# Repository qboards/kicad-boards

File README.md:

# QBoard Printed Circuit Boards

All development boards made in Kicad

## Breakout boards

* [BB-Led](bb-led) - Single SMD (0805) LED breakout board
* [BB-LedBar](bb-ledbar) - Eight SMD (0805) LED breakout board
* [BB-ButtonBar](bb-buttonbar) - Four tactile switch breakout board
* [BB-SOIC-SSOP-8](bb-soic-ssop-8) - Breakout board for SOIC/SSOP ICs up to 8 pins
* [BB-SOIC-SSOP-16](bb-soic-ssop-16) - Breakout board for SOIC/SSOP ICs up to 16 pins
* [BB-SOIC-SSOP-24](bb-soic-ssop-24) - Breakout board for SOIC/SSOP ICs up to 24 pins
* [BB-SOT89-SOT223](bb-sot89-sot223) - Breakout board for SOT-89 / SOT-223 smd transitor packages
* [BB-TQFP-QFN](bb-tqfp-qfn-32) - Breakout board for TQFP/QFN ICs with 32 pins
* [BB-XTAL](bb-xtal) - Breakout board for Crystal and its capacitors
* [BB-AVRISP](bb-avrisp) - Breakout for 10- and 6-pin AVR ISP connectors

## Development tools

* [DEV-UUSBPSU](dev-uusb-psu) - Small 3.3V/5V breadboard power supply with microUSB connector

# About QBoards

QBoard is a project to create a collection of small tools that facilitate Electronic 
Engineering, using readily available parts. For PCBs we aim to create well designed 
boards that can be purchased by low cost vendors such as <a href="https://www.seeedstudio.com">
Seeed Studio</a>, <a href="https://oshpark.com/">OSHPark</a> or <a href="https://dirtypcbs.com">DirtyPCBs</a>.

# Licensing

This work is licensed under a [Creative Commons Attribution-ShareAlike 4.0 International License](http://creativecommons.org/licenses/by-sa/4.0/).

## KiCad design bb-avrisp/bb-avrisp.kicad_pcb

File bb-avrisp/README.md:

# QBoard BB-AVRISP

Breakout for 10 and 6 pin AVR ISP (In-system Programming) connectors

# Downloads

* [Gerbers](output/gerbers.zip)
* [Schematic](output/schematic.pdf)

# Buy

* [Buy protopack (10) from DirtyPcbs](https://dirtypcbs.com/store/designer/details/qboards/6508/qboard-bb-avrisp)

# About QBoards

See [here](https://github.com/qboards/kicad-boards#about-qboards)

# Licensing

See [here](https://github.com/qboards/kicad-boards#licensing)

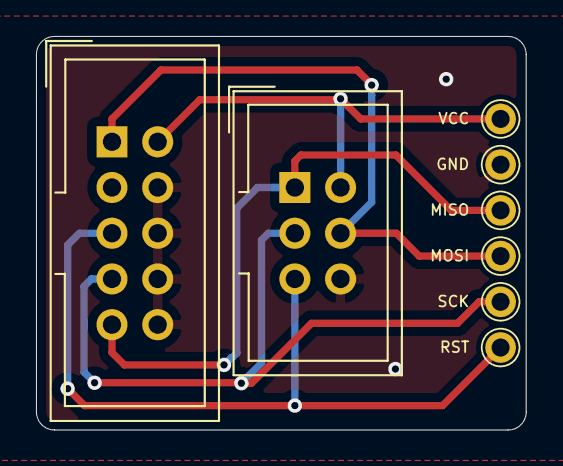
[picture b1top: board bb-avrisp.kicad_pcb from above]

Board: 2 copper layers, 27.2 x 21.9 mm, 9 parts (1 on the bottom side), 6 nets.

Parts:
BB_AVRISP: LOGO_BRD_REF; logo_url-3mm
J1, J2, J3, J4, J5, J8: Conn_01x01_Male; PinHeader_1x01_P2.54mm_Vertical
J6: Conn_02x03_Odd_Even; IDC-Header_2x03_P2.54mm_Vertical
J7: Conn_02x05_Odd_Even; IDC-Header_2x05_P2.54mm_Vertical

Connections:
GND: J6.6, J7.4, J7.6, J7.8, J7.10, J8.1
MISO: J2.1, J6.1, J7.9
MOSI: J3.1, J6.4, J7.1
RST: J5.1, J6.5, J7.5
SCK: J4.1, J6.3, J7.7
VCC: J1.1, J6.2, J7.2

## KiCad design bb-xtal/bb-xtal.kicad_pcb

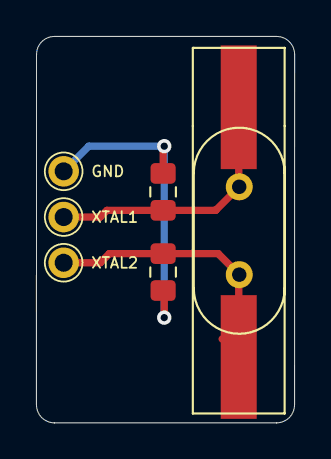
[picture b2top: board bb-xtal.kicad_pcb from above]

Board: 2 copper layers, 14.3 x 21.5 mm, 8 parts (1 on the bottom side), 3 nets.

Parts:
BB_XTAL: LOGO_BRD_REF; logo_url-5mm
C1, C2: C; C_0805_2012Metric_Pad1.15x1.40mm_HandSolder
J1, J2, J3: Conn_01x01_Male; PinHeader_1x01_P2.54mm_Vertical
Y1: Crystal; Crystal_HC49-4H_Vertical
Y2: Crystal; Crystal_SMD_HC49-SD_HandSoldering

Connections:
unnamed: C1.1, J2.1, Y1.1, Y2.1
unnamed: C1.2, C2.1, J3.1
unnamed: C2.2, J1.1, Y1.2, Y2.2

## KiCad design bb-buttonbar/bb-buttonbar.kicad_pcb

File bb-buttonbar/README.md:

# QBoard BB-ButtonBar

Array of 4 tactile switches on a breakout board. Includes (common) pull-up or
pull-down resistor

# Downloads

* [Gerbers](output/gerbers.zip)
* [Schematic](output/schematic.pdf)

# Buy

* [Buy protopack (10) from DirtyPcbs](https://dirtypcbs.com/store/designer/details/qboards/6509/qboard-bb-button-bar)

# About QBoards

See [here](https://github.com/qboards/kicad-boards#about-qboards)

# Licensing

See [here](https://github.com/qboards/kicad-boards#licensing)

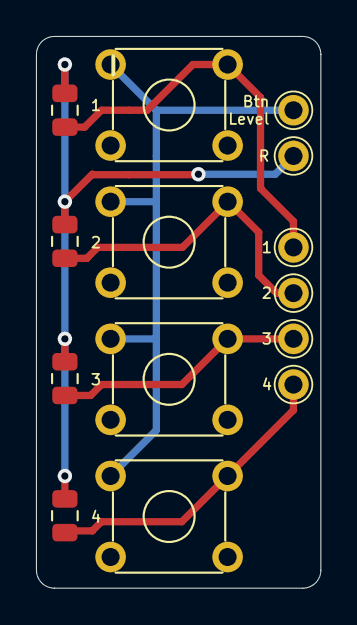
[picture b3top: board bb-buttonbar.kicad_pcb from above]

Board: 2 copper layers, 15.8 x 30.7 mm, 15 parts (1 on the bottom side), 6 nets.

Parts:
1, 2, 3, 4: SW_Push; SW_TH_Tactile_Omron_B3F-10xx
BB_BUTTONBAR: LOGO_BRD_REF; logo_url-3mm
J1, J2, J3, J4: Conn_01x01_Male; PinHeader_1x01_P2.54mm_Vertical_dual
LEVEL1, LEVEL2: Conn_01x01_Male; PinHeader_1x01_P2.54mm_Vertical_dual
R1, R2, R3, R4: R; R_0805_2012Metric

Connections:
unnamed: 1.2, J1.1, R1.2
unnamed: 2.2, J2.1, R2.2
unnamed: 3.2, J3.1, R3.2
unnamed: 4.2, J4.1, R4.2
unnamed: 1.1, 2.1, 3.1, 4.1, LEVEL1.1
unnamed: LEVEL2.1, R1.1, R2.1, R3.1, R4.1

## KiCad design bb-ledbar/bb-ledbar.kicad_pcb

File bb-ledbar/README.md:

# QBoard BB-LedBar

Array of eight SMD leds (0805) on a breakout board that fits between the bus and the main grid of a breadboard. One side is common cathode, other side common anode.

# Downloads

* [Gerbers](output/gerbers.zip)
* [Schematic](output/schematic.pdf)

# Buy

* [Buy protopack (10) from DirtyPcbs](https://dirtypcbs.com/store/designer/details/qboards/6508/qboard-bb-led)

# About QBoards

See [here](https://github.com/qboards/kicad-boards#about-qboards)

# Licensing

See [here](https://github.com/qboards/kicad-boards#licensing)

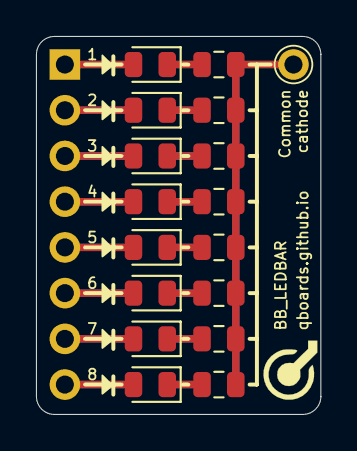
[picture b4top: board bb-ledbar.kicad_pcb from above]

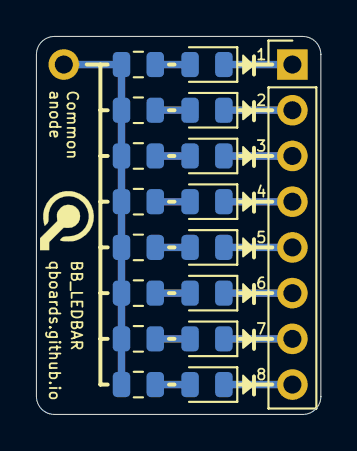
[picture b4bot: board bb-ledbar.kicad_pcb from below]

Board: 2 copper layers, 15.8 x 21.0 mm, 36 parts (18 on the bottom side), 25 nets.

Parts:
BB_LEDBAR: LOGO_BRD_REF; logo_url-3mm
BB_LEDBAR#2: LOGO_BRD_REF; logo_url-3mm
DA_1, DA_2, DA_3, DA_4, DA_5, DA_6, DA_7, DA_8: LED; LED_0805_2012Metric
DB_1, DB_2, DB_3, DB_4, DB_5, DB_6, DB_7, DB_8: LED; LED_0805_2012Metric
J1: Conn_01x08_Male; PinHeader_1x08_P2.54mm_Vertical
J2: Conn_01x01_Male; PinHeader_1x01_P2.54mm_Vertical
RA_1, RA_2, RA_3, RA_4, RA_5, RA_6, RA_7, RA_8: R; R_0805_2012Metric
RB_1, RB_2, RB_3, RB_4, RB_5, RB_6, RB_7, RB_8: R; R_0805_2012Metric

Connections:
unnamed: DA_1.1, RA_1.1
unnamed: DA_1.2, DB_1.1, J1.1
unnamed: DA_2.1, RA_2.1
unnamed: DA_2.2, DB_2.1, J1.2
unnamed: DA_3.1, RA_3.1
unnamed: DA_3.2, DB_3.1, J1.3
unnamed: DA_4.1, RA_4.1
unnamed: DA_4.2, DB_4.1, J1.4
unnamed: DA_5.1, RA_5.1
unnamed: DA_5.2, DB_5.1, J1.5
unnamed: DA_6.1, RA_6.1
unnamed: DA_6.2, DB_6.1, J1.6
unnamed: DA_7.1, RA_7.1
unnamed: DA_7.2, DB_7.1, J1.7
unnamed: DA_8.1, RA_8.1
unnamed: DA_8.2, DB_8.1, J1.8
unnamed: DB_1.2, RB_1.1
unnamed: DB_2.2, RB_2.1
unnamed: DB_3.2, RB_3.1
unnamed: DB_4.2, RB_4.1
unnamed: DB_5.2, RB_5.1
unnamed: DB_6.2, RB_6.1
unnamed: DB_7.2, RB_7.1
unnamed: DB_8.2, RB_8.1
unnamed: J2.1, RA_1.2, RA_2.2, RA_3.2, RA_4.2, RA_5.2, RA_6.2, RA_7.2, RA_8.2, RB_1.2, RB_2.2, RB_3.2, RB_4.2, RB_5.2, RB_6.2, RB_7.2, RB_8.2

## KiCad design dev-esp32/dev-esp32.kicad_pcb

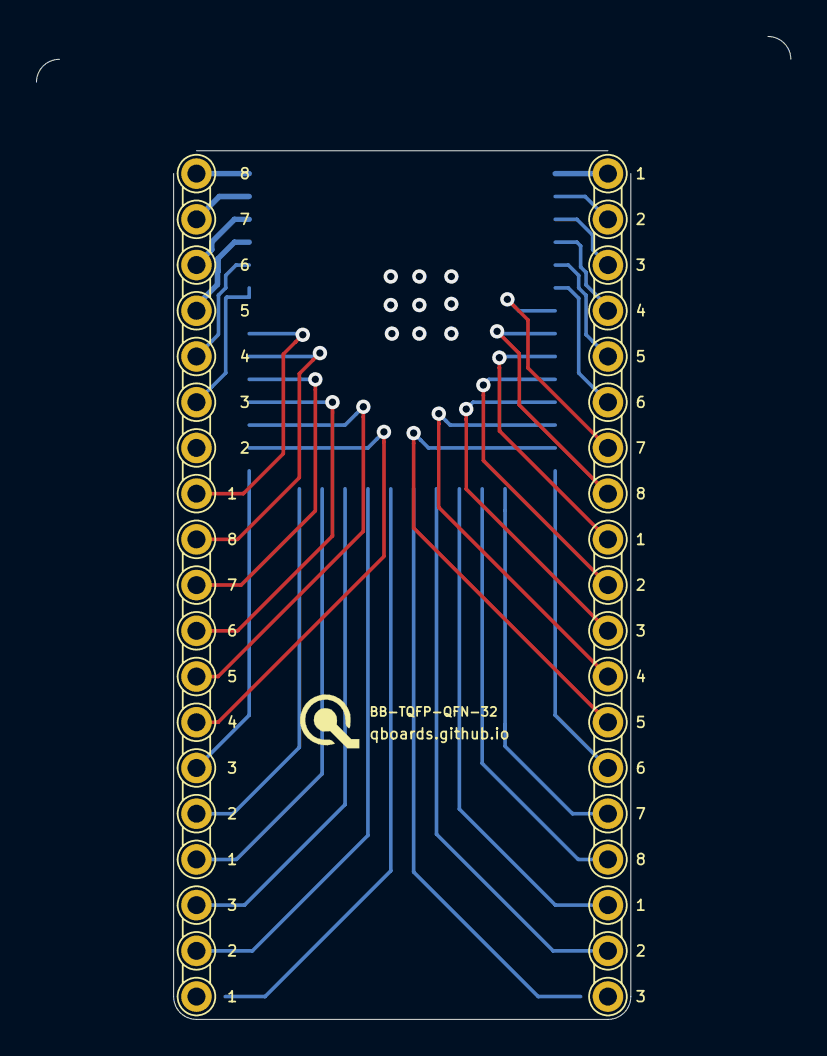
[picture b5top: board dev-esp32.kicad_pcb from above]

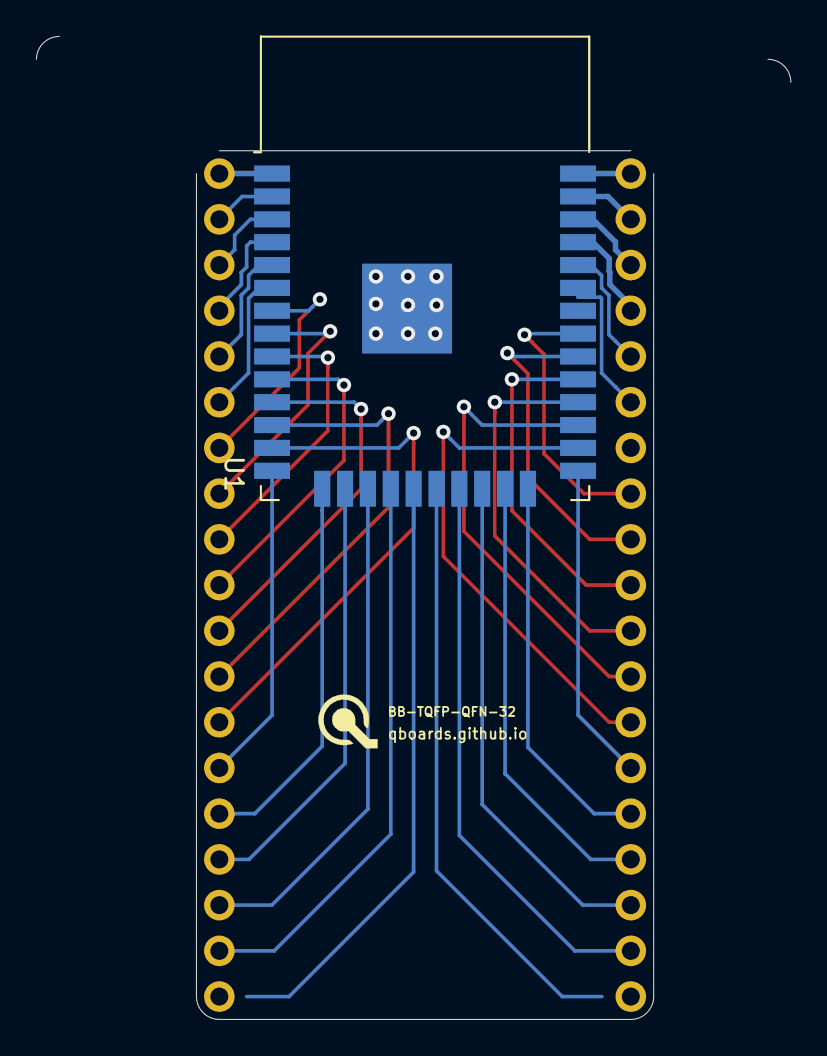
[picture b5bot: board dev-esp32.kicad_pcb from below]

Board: 2 copper layers, 41.9 x 54.6 mm, 9 parts (2 on the bottom side), 35 nets.

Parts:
BB-TQFP-QFN-32, BB-TQFP-QFN-32#2: LOGO_BRD_REF; logo_url-3mm
J1_8, J9_16, J23_30, J31_38: Conn_01x08_Male; PinHeader_1x08_P2.54mm_Vertical
J17_19, J20_22: Conn_01x03_Male; PinHeader_1x03_P2.54mm_Vertical
U1: ESP32-WROOM-32

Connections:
unnamed: J1_8.1, J9_16.7, J31_38.8, U1.1, U1.15, U1.38
unnamed: J1_8.2, U1.2
unnamed: J1_8.3, U1.3
unnamed: J1_8.4, U1.4
unnamed: J1_8.5, U1.5
unnamed: J1_8.6, U1.6
unnamed: J1_8.7, U1.7
unnamed: J1_8.8, U1.8
unnamed: J9_16.1, U1.9
unnamed: J9_16.2, U1.10
unnamed: J9_16.3, U1.11
unnamed: J9_16.4, U1.12
unnamed: J9_16.5, U1.13
unnamed: J9_16.6, U1.14
unnamed: J9_16.8, U1.16
unnamed: J17_19.1, U1.17
unnamed: J17_19.2, U1.18
unnamed: J17_19.3, U1.19
unnamed: J20_22.1, U1.20
unnamed: J20_22.2, U1.21
unnamed: J20_22.3, U1.22
unnamed: J23_30.1, U1.23
unnamed: J23_30.2, U1.24
unnamed: J23_30.3, U1.25
unnamed: J23_30.4, U1.26
unnamed: J23_30.5, U1.27
unnamed: J23_30.6, U1.28
unnamed: J23_30.7, U1.29
unnamed: J23_30.8, U1.30
unnamed: J31_38.1, U1.31
unnamed: J31_38.3, U1.33
unnamed: J31_38.4, U1.34
unnamed: J31_38.5, U1.35
unnamed: J31_38.6, U1.36
unnamed: J31_38.7, U1.37

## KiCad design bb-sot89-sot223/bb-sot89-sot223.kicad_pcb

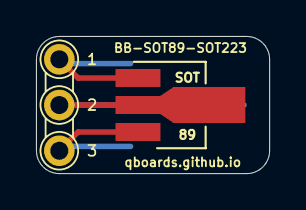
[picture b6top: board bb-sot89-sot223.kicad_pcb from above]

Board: 2 copper layers, 13.0 x 7.6 mm, 3 parts (1 on the bottom side), 3 nets.

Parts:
J1: Conn_01x03_Male; PinHeader_1x03_P2.54mm_Vertical_dual
SOT: AZ1117-3.3; SOT-89-3_Handsoldering
SOT-223: LM337_SOT223; SOT-223-3_TabPin2

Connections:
unnamed: J1.1, SOT.1, SOT-223.3
unnamed: J1.2, SOT.2, SOT-223.2
unnamed: J1.3, SOT.3, SOT-223.1

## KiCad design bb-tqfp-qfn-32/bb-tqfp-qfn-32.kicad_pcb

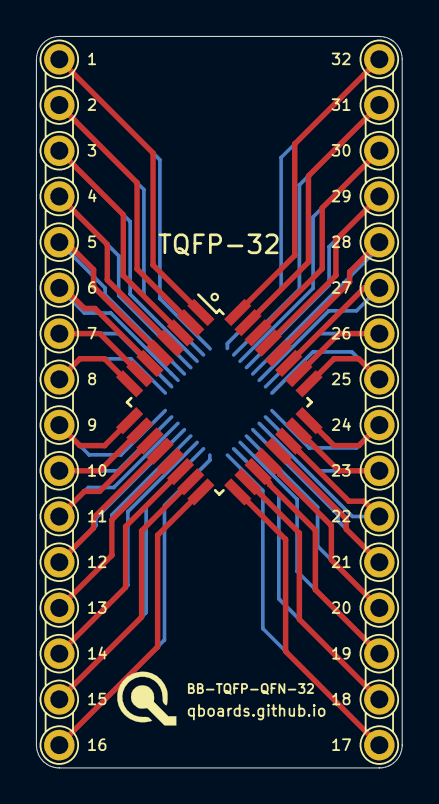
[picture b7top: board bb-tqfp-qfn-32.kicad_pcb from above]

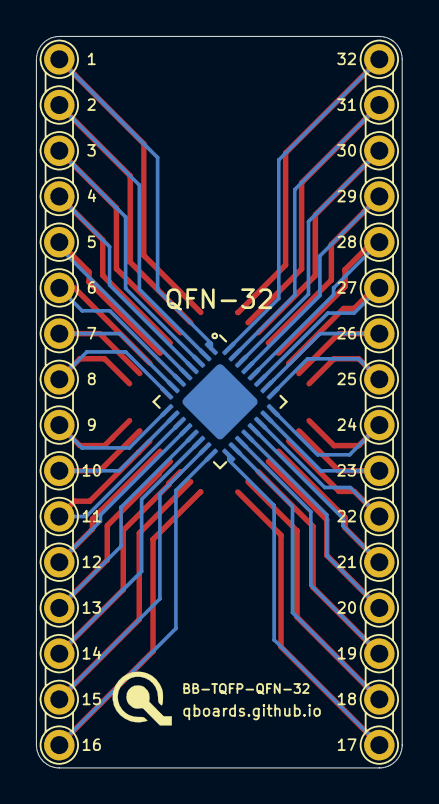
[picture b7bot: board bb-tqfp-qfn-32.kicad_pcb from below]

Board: 2 copper layers, 20.3 x 40.6 mm, 8 parts (2 on the bottom side), 32 nets.

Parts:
BB-TQFP-QFN-32, BB-TQFP-QFN-32#2: LOGO_BRD_REF; logo_url-3mm
J1, J2, J3, J4: Conn_01x08_Male; PinHeader_1x08_P2.54mm_Vertical_dual
QFN-32: IC-32Q; QFN-32-1EP_5x5mm_P0.5mm_EP3.1x3.1mm
TQFP-32: IC-32Q; TQFP-32_7x7mm_P0.8mm

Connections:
unnamed: J1.1, QFN-32.32, TQFP-32.1
unnamed: J1.2, QFN-32.31, TQFP-32.2
unnamed: J1.3, QFN-32.30, TQFP-32.3
unnamed: J1.4, QFN-32.29, TQFP-32.4
unnamed: J1.5, QFN-32.28, TQFP-32.5
unnamed: J1.6, QFN-32.27, TQFP-32.6
unnamed: J1.7, QFN-32.26, TQFP-32.7
unnamed: J1.8, QFN-32.25, TQFP-32.8
unnamed: J2.1, QFN-32.24, TQFP-32.9
unnamed: J2.2, QFN-32.23, TQFP-32.10
unnamed: J2.3, QFN-32.22, TQFP-32.11
unnamed: J2.4, QFN-32.21, TQFP-32.12
unnamed: J2.5, QFN-32.20, TQFP-32.13
unnamed: J2.6, QFN-32.19, TQFP-32.14
unnamed: J2.7, QFN-32.18, TQFP-32.15
unnamed: J2.8, QFN-32.17, TQFP-32.16
unnamed: J3.1, QFN-32.16, TQFP-32.17
unnamed: J3.2, QFN-32.15, TQFP-32.18
unnamed: J3.3, QFN-32.14, TQFP-32.19
unnamed: J3.4, QFN-32.13, TQFP-32.20
unnamed: J3.5, QFN-32.12, TQFP-32.21
unnamed: J3.6, QFN-32.11, TQFP-32.22
unnamed: J3.7, QFN-32.10, TQFP-32.23
unnamed: J3.8, QFN-32.9, TQFP-32.24
unnamed: J4.1, QFN-32.8, TQFP-32.25
unnamed: J4.2, QFN-32.7, TQFP-32.26
unnamed: J4.3, QFN-32.6, TQFP-32.27
unnamed: J4.4, QFN-32.5, TQFP-32.28
unnamed: J4.5, QFN-32.4, TQFP-32.29
unnamed: J4.6, QFN-32.3, TQFP-32.30
unnamed: J4.7, QFN-32.2, TQFP-32.31
unnamed: J4.8, QFN-32.1, TQFP-32.32

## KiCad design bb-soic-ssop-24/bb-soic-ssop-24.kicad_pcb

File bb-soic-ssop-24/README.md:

# QBoard BB-SOIC-SSOP-24

Breakout board for SOIC/SSOP IC packages up to 24 pins. Uses extra long and wide pads so
a lot of different packages should fit. To use, just solder your IC on the SOIC or the
SSOP side (only ever use one IC, as the header pins are shared) and you can breadboard
your IC.

Package properties:

|             |  SOIC  |   SSOP  |
|:-----------:|:------:|:-------:|
| Pad count   | 24     | 24      |
| Pad pitch   | 1.27mm | 0.635mm |
| Pad width   | 0.8mm  | 0.4mm   |
| Pad length  | 4.2mm  | 4.2mm   |
| Row spacing | 5.2mm  | 5.2mm   |

# Downloads

* [Gerbers](output/gerbers.zip)
* [Schematic](output/schematic.pdf)

# Buy

* [Buy protopack (10) from DirtyPcbs](https://dirtypcbs.com/store/designer/details/qboards/6376/qboard-bb-soic-ssop-24)

# About QBoards

See [here](https://github.com/qboards/kicad-boards#about-qboards)

# Licensing

See [here](https://github.com/qboards/kicad-boards#licensing)

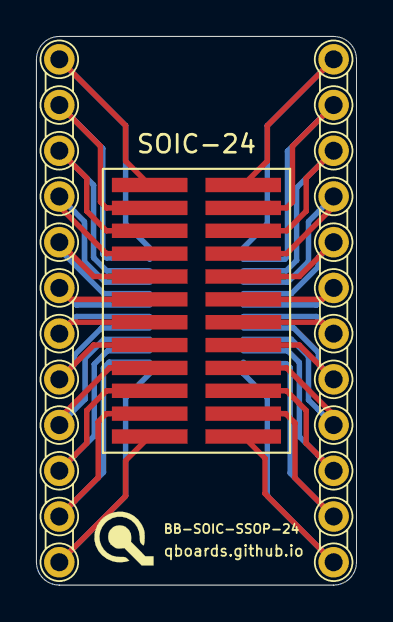
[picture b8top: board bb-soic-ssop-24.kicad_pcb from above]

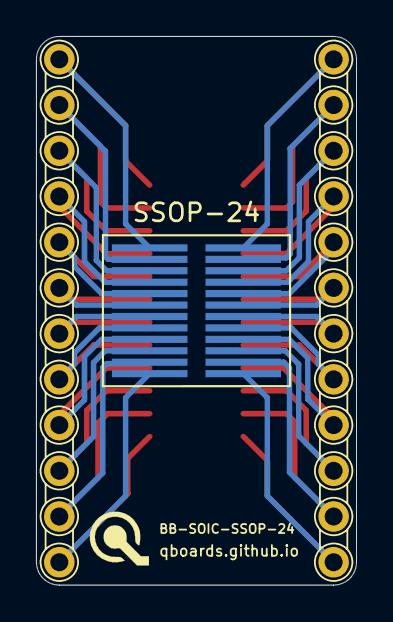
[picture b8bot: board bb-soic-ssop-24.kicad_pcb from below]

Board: 2 copper layers, 17.8 x 30.5 mm, 6 parts (2 on the bottom side), 24 nets.

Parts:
BB-SOIC-SSOP-24, BB-SOIC-SSOP-24#2: LOGO_BRD_REF; logo_url-3mm
J1, J2: Conn_01x12_Male; PinHeader_1x012_P2.54mm_Vertical_dual
SOIC-24: IC-24; SOIC-24
SSOP-24: IC-24; SSOP-24

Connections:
unnamed: J1.1, SOIC-24.1, SSOP-24.12
unnamed: J1.2, SOIC-24.2, SSOP-24.11
unnamed: J1.3, SOIC-24.3, SSOP-24.10
unnamed: J1.4, SOIC-24.4, SSOP-24.9
unnamed: J1.5, SOIC-24.5, SSOP-24.8
unnamed: J1.6, SOIC-24.6, SSOP-24.7
unnamed: J1.7, SOIC-24.7, SSOP-24.6
unnamed: J1.8, SOIC-24.8, SSOP-24.5
unnamed: J1.9, SOIC-24.9, SSOP-24.4
unnamed: J1.10, SOIC-24.10, SSOP-24.3
unnamed: J1.11, SOIC-24.11, SSOP-24.2
unnamed: J1.12, SOIC-24.12, SSOP-24.1
unnamed: J2.1, SOIC-24.13, SSOP-24.24
unnamed: J2.2, SOIC-24.14, SSOP-24.23
unnamed: J2.3, SOIC-24.15, SSOP-24.22
unnamed: J2.4, SOIC-24.16, SSOP-24.21
unnamed: J2.5, SOIC-24.17, SSOP-24.20
unnamed: J2.6, SOIC-24.18, SSOP-24.19
unnamed: J2.7, SOIC-24.19, SSOP-24.18
unnamed: J2.8, SOIC-24.20, SSOP-24.17
unnamed: J2.9, SOIC-24.21, SSOP-24.16
unnamed: J2.10, SOIC-24.22, SSOP-24.15
unnamed: J2.11, SOIC-24.23, SSOP-24.14
unnamed: J2.12, SOIC-24.24, SSOP-24.13

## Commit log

2019-06-10 Added dev-uusb-psu project
2019-06-10 BB-led inital commit
2019-06-10 Updated pin connectors
2019-06-10 Fixed sheet metadata
2019-06-10 Feature/bb led (#1)
    * BB-led inital commit
    * Updated pin connectors
    * Fixed sheet metadata
2019-06-10 Updated connectors
2019-06-10 Fixed metadata
2019-06-10 Feature/dev uusbpsu (#2)
    * Added dev-uusb-psu project
    * Updated connectors
    * Fixed metadata
2019-10-13 Added BB-SOIC-SSOP-16
2019-10-13 Added gerbers
2019-10-13 Added readme
2019-10-13 Added schematic
2019-10-13 Added schematc in color
2019-10-13 Updated main readme
2019-10-13 Added render
2019-10-13 Updated render
2019-10-13 Feature/bb soic ssop 16 (#3)
    * Added BB-SOIC-SSOP-16
    * Updated readme
    * Updated main readme
2019-10-13 Added BB-LED output
2019-10-13 Removed duplicate license file
2019-10-13 Fixed bb-led output
2019-10-13 Added output and fixed readme for uusb-psu
2019-10-13 Fixed typo
2019-10-13 Added SOIC board
2019-10-13 Added SOIC board (#4)
2019-10-13 Made SOIC-SSOP-8 connector labels invisible
2019-10-13 Fixed issue with board outline in gerbers
2019-10-14 Added buy link for some boards
2019-10-14 Added BB-SOIC-SSOP-24 board
2019-10-14 Added DirtyPCB link
2019-10-14 Added main link to board
2019-10-14 Feature/bb soic ssop 24 (#5)
    * Added BB-SOIC-SSOP-24 board
    * Added DirtyPCB link
    * Added main link to board
2019-10-14 Added BB-TQFP-QFN-32 board
2019-10-14 Fixed list in readme
2019-10-14 Feature/bb tqfp qfn 32 (#6)
    * Added BB-TQFP-QFN-32 board
    * Fixed list in readme
2019-10-16 Added BB-SOT89-SOT223 board
2019-10-16 Added BB-SOT89-SOT223 board (#7)
2019-10-16 Switched all DirtyPCB links to https
2019-11-14 Initial WIP
2021-01-27 Initial led bar
2021-01-27 Added schematic and render
2021-01-27 Added store url
2021-01-27 Added ledbar to main readme
2021-01-27 Added bb-ledbar: Squashed commit of the following:
    commit 2e9ef70b26d5fff67fedcedfce095505f0a58d6c
    Author: Wilco Tomassen <wilco@wilcotomassen.nl>
    Date: Wed Jan 27 18:29:01 2021 +0100
    Added ledbar to main readme
    commit b670a6cd02294eb120579e1bed9e5d485c929278
    Author: Wilco Tomassen <wilco@wilcotomassen.nl>
2021-01-27 Initial buttonbar
2021-01-27 Updated readmes
2021-01-27 Added xtal
2021-01-28 Added bb-avrisp
